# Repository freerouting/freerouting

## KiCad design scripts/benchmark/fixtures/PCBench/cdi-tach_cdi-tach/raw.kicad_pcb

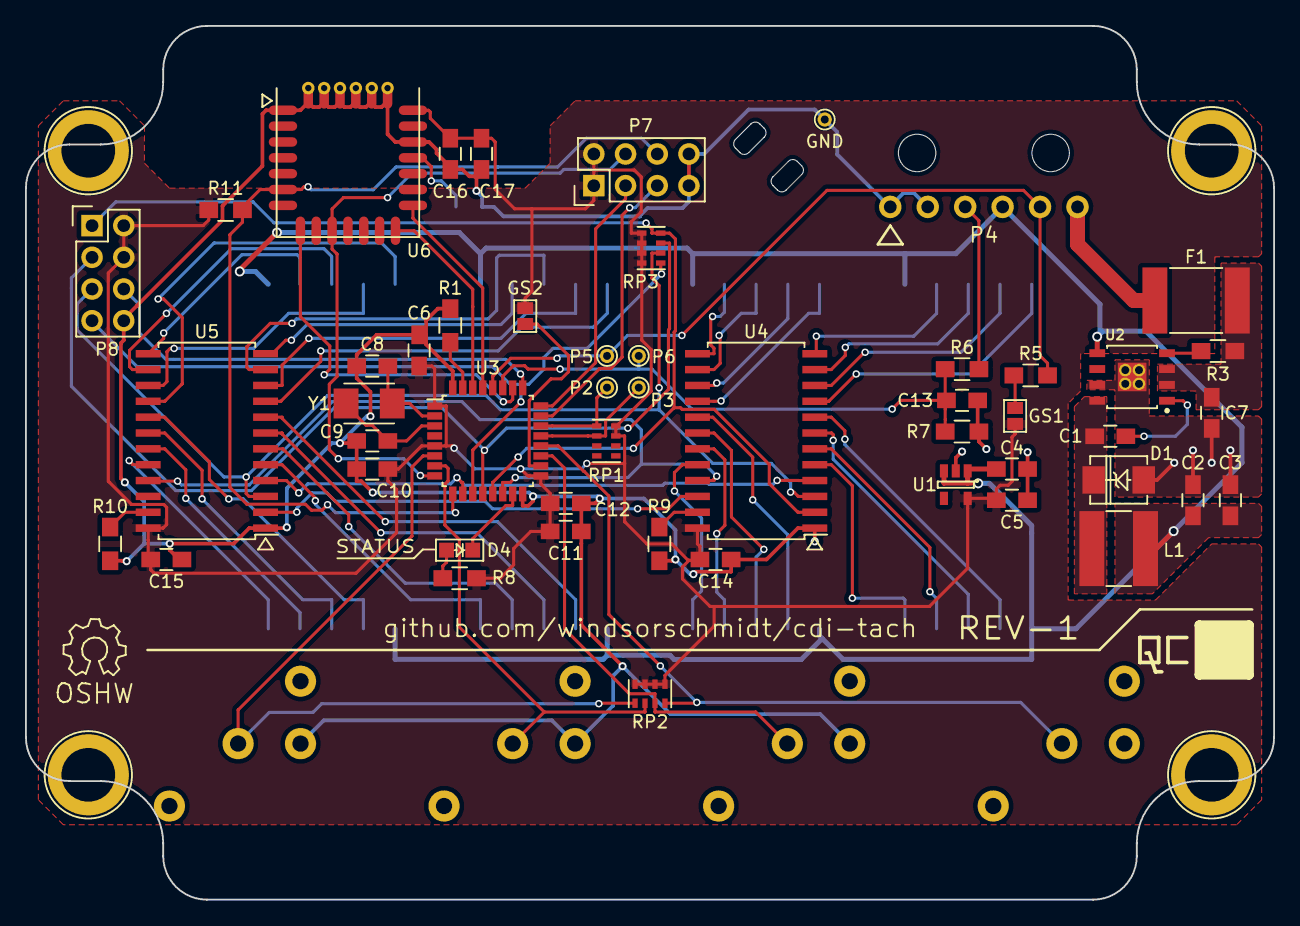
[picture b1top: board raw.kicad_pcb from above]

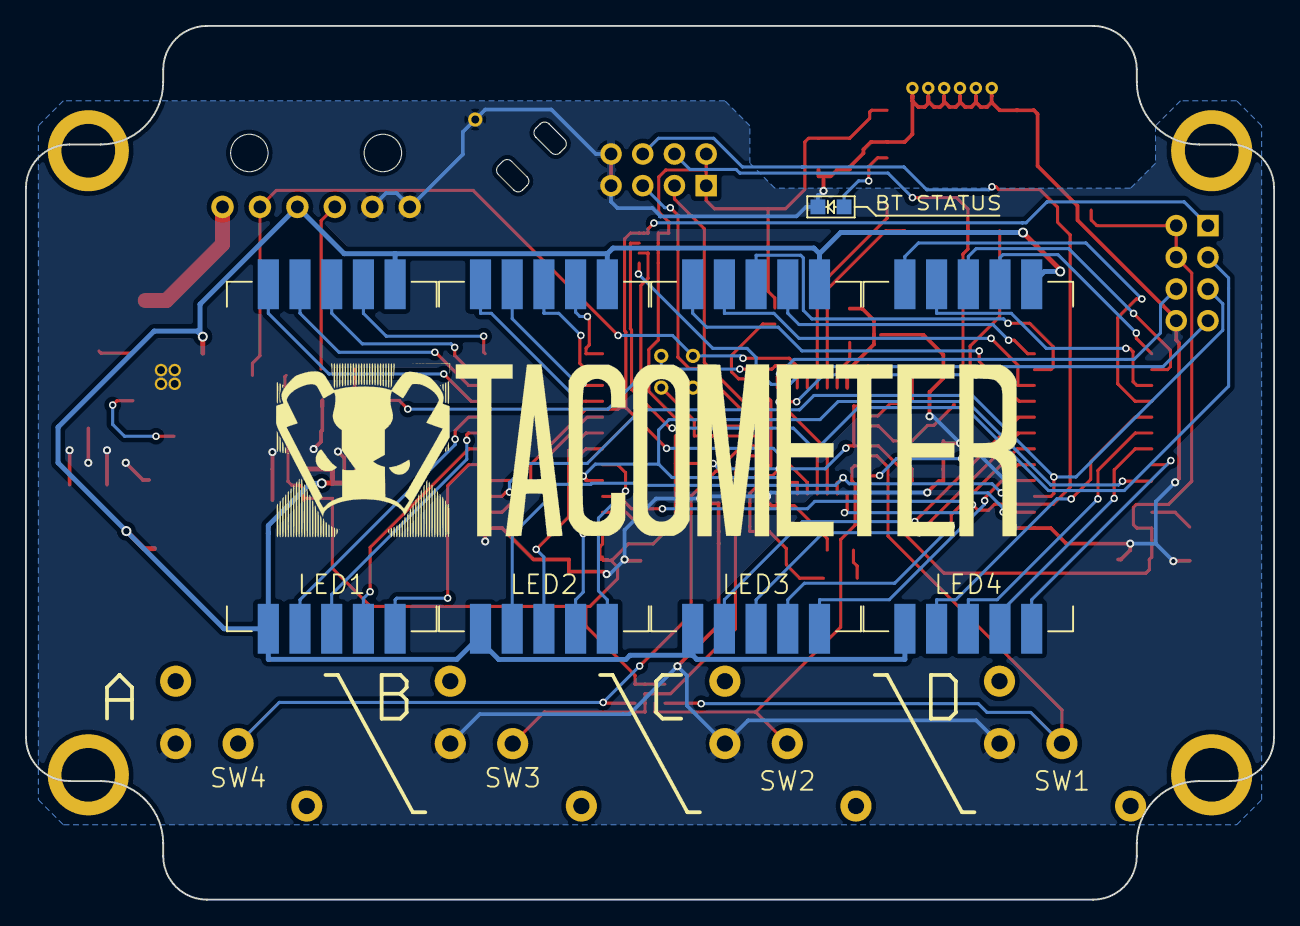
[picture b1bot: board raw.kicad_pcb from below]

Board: 2 copper layers, 100.0 x 70.0 mm, 70 parts (11 on the bottom side), 74 nets.

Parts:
ART1: badger_logo; badger_face_logo
ART2: OSHW_logo; Symbol_OSHW-Logo_SilkScreen
ART3: part_logo; tacometer_logo
ART4: QC_label; label_qc
C1, C6, C10, C12, C17: 100nF; C_0805_HandSoldering
C2, C3: 22uF; C_0805_HandSoldering
C4, C5, C14, C15: 1uF; C_0805_HandSoldering
C7, C16: 10uF; C_0805_HandSoldering
C8, C9: 18pF; C_0805_HandSoldering
C11: 4.7uF; C_0805_HandSoldering
C13: 22nF; C_0805_HandSoldering
D1: SSB44; Diode_SSB44
D4: STATUS; LED_0805
D5: BT STATUS; LED_0805
F1: 3.7A Polyswitch; Fuse_Resettable
GND: GND; PINTST
GS1: SPD_PU; GS2
GS2: MODE; GS2
L1: 6.8uH; Inductor_Bourns_SRN6045_6mm
LED1, LED2, LED3, LED4: ACSA08-51SEKWA
MNT1, MNT6: zip_tie_slot; MOUNT_ZIP_TIE
MNT2, MNT3, MNT4, MNT5: 4mm_screw; Screw_M4
P2: SDA; PINTST
P3: SCL; PINTST
P4: PWR_SPD_TACH; micro-fit_1x6_ra
P5: SPEED; PINTST
P6: TACH; PINTST
P7: DEBUG; Pin_Header_Straight_2x04
P8: LCD; Pin_Header_Straight_2x04
PCB enclosure: PCB_enclosure; pcb_enclosure
R1, R5, R9, R10: 3K; R_0805_HandSoldering
R3, R6: 100K; R_0805_HandSoldering
R7: 12.1K; R_0805_HandSoldering
R8: 39; R_0805_HandSoldering
R11: 10K; R_0805_HandSoldering
RP1, RP2, RP3: 4.7K; R_Cat16-4
SW1: A; pushbutton_marquardt_6450
SW2: B; pushbutton_marquardt_6450
SW3: C; pushbutton_marquardt_6450
SW4: D; pushbutton_marquardt_6450
U1: MIC5504-3.3YM5; SOT-23-5
U2: ADP2302ARDZ-5.0; ADP2302_SOIC8
U3: STM32F030K6T6; LQFP-32_7x7mm_Pitch0.8mm
U4, U5: CAT4016; SOIC-24_7.5x15.4mm_Pitch1.27mm
U6: AMS002-S
Y1: 7A-8.000MAAE-T; crystal_txc_7a_5x3.2mm

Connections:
+3V3: C5.1, C6.2, C10.2, C11.1, C12.1, C14.2, C15.2, C16.1, C17.1, GS1.2, GS2.2, P7.1, P7.2, P8.2, P8.4, R8.2, R11.1, RP1.7, RP1.8, RP2.5, RP2.6, RP2.7, RP2.8, RP3.1, RP3.2, RP3.3, RP3.4, U1.5, U3.1, U3.5, U3.17, U4.24, U5.24, U6.21
+5V: C2.1, C3.1, C4.1, L1.2, LED1.1, LED1.6, LED2.1, LED2.6, LED3.1, LED3.6, LED4.1, LED4.6, P4.3, U1.1, U1.3, U2.5
+12V: F1.1, P4.1
BTN_A: RP2.1, SW1.1, U3.6
BTN_B: RP2.2, SW2.1, U3.7
BTN_C: RP2.3, SW3.1, U3.19
BTN_D: RP2.4, SW4.1, U3.20
BT_CONN: U3.29, U6.15
BT_NRST: U3.26, U6.8
BT_STRM: U3.30, U6.14
GND: C2.2, C3.2, C4.2, C5.2, C6.1, C7.1, C8.1, C9.1, C10.1, C11.2, C12.2, C13.1, C14.1, C15.1, C16.2, C17.2, D1.1, D5.1, GND.1, P4.5, P4.6, P7.7, P7.8, P8.8, R1.2, R7.2, R9.2, R10.2, SW1.2, SW2.2, SW3.2, SW4.2, U1.2, U2.7, U2.9, U3.16, U3.32, U4.1, U5.1, U6.1, U6.19, U6.22, U6.23, U6.24, U6.25, U6.26, U6.27
LCD_RST: P8.6, U3.25
LED1_A: LED1.8, U4.11
LED1_B: LED1.7, U4.12
LED1_C: LED1.4, U4.6
LED1_D: LED1.3, U4.7
LED1_DP: LED1.5, U4.5
LED1_E: LED1.2, U4.8
LED1_F: LED1.9, U4.10
LED1_G: LED1.10, U4.9
LED2_A: LED2.8, U4.14
LED2_B: LED2.7, U4.13
LED2_C: LED2.4, U4.19
LED2_D: LED2.3, U4.18
LED2_DP: LED2.5, U4.20
LED2_E: LED2.2, U4.17
LED2_F: LED2.9, U4.15
LED2_G: LED2.10, U4.16
LED3_A: LED3.8, U5.11
LED3_B: LED3.7, U5.12
LED3_C: LED3.4, U5.6
LED3_D: LED3.3, U5.7
LED3_DP: LED3.5, U5.5
LED3_E: LED3.2, U5.8
LED3_F: LED3.9, U5.10
LED3_G: LED3.10, U5.9
LED4_A: LED4.8, U5.14
LED4_B: LED4.7, U5.13
LED4_C: LED4.4, U5.19
LED4_D: LED4.3, U5.18
LED4_DP: LED4.5, U5.20
LED4_E: LED4.2, U5.17
LED4_F: LED4.9, U5.15
LED4_G: LED4.10, U5.16
LED_BLANK: U3.14, U4.21, U5.21
LED_LATCH: U3.10, U4.4, U5.4
unnamed: C1.1, D1.2, L1.1, U2.8
unnamed: C1.2, U2.1
unnamed: C7.2, F1.2, R3.2, U2.2, U2.3
unnamed: C8.2, U3.2, Y1.2
unnamed: C9.2, U3.3, Y1.1
unnamed: D4.1, U3.15
unnamed: D4.2, R8.1
unnamed: D5.2, U6.18
unnamed: GS1.1, R5.2
unnamed: GS2.1, U3.18
unnamed: P2.1, RP1.1, U3.22
unnamed: P3.1, RP1.2, U3.21
unnamed: P4.4, R6.1
unnamed: R1.1, U3.31
unnamed: R3.1, U2.4
unnamed: R9.1, U4.23
unnamed: R10.1, U5.23
unnamed: U4.22, U5.2
SPEED: P4.2, P5.1, R5.1, U3.28
SPI_CS: P8.7, RP3.5, U3.11
SPI_MISO: P8.3, RP3.7, U3.12
SPI_MOSI: P8.1, RP3.8, U3.13, U4.2
SPI_SCK: P8.5, RP3.6, U4.3, U5.3
SWCLK: P7.3, U3.24
SWDIO: P7.5, U3.23
TACH: C13.2, P6.1, R6.2, R7.1, U3.27
USART_RX: P7.6, R11.2, U3.9, U6.6
USART_TX: P7.4, U3.8, U6.10

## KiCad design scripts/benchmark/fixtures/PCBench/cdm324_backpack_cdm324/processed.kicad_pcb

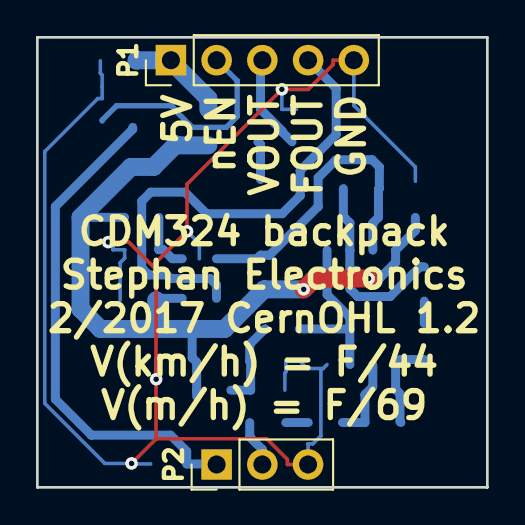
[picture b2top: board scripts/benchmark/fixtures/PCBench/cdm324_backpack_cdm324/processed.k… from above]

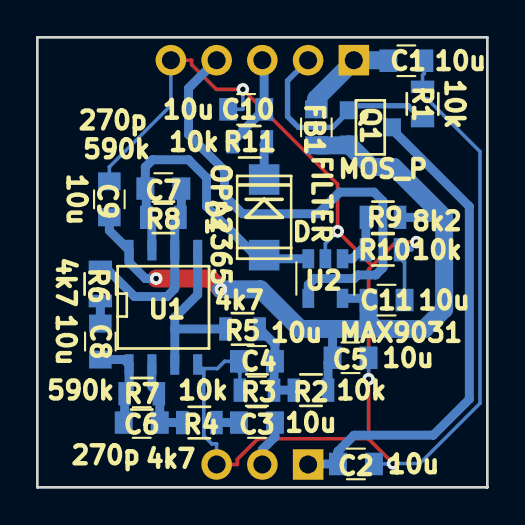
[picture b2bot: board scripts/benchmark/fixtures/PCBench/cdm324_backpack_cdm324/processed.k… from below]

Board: 2 copper layers, 25.0 x 25.0 mm, 29 parts (27 on the bottom side), 18 nets.

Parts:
C1, C2, C3, C4, C5, C8, C9, C10, C11: 10u; C_0805
C6, C7: 270p; C_0805
D1: D; DIODE_SMA
FB1: FILTER; C_0805
P1: CONN_01X05; Pin_Header_Straight_1x05_Pitch2.54mm
P2: CONN_01X03; Pin_Header_Straight_1x03_Pitch2.54mm
Q1: MOS_P; SOT23-3
R1, R2, R3, R10, R11: 10k; R_0805
R4, R5, R6: 4k7; R_0805
R7, R8: 590k; R_0805
R9: 8k2; R_0805
U1: OPA2365; SOIC-8-N
U2: MAX9031; SOT-23-5

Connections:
+5V: C1.1, FB1.1, P1.1
/FOUT: P1.4, U2.4
/VOUT: C10.1, P1.3, R11.2
/nEN: P1.2, Q1.1, R1.1
GND: C1.2, C2.2, C4.2, C5.2, C9.2, C10.2, C11.2, P1.5, P2.3, R1.2, R3.2, R10.2, U1.4, U2.2
unnamed: C2.1, P2.1, Q1.3
unnamed: C3.1, P2.2
unnamed: C3.2, R4.1
unnamed: C4.1, R2.2, R3.1, R5.1
unnamed: C6.1, R4.2, R7.1, U1.2
unnamed: C6.2, C8.2, R7.2, U1.1
unnamed: C7.1, R6.1, R8.2, U1.6
unnamed: C7.2, D1.2, R8.1, U1.7, U2.3
unnamed: C8.1, R6.2
unnamed: C5.1, C9.1, C11.1, FB1.2, Q1.2, R2.1, R9.1, U1.8, U2.5
unnamed: D1.1, R11.1
unnamed: R5.2, U1.3, U1.5
unnamed: R9.2, R10.1, U2.1

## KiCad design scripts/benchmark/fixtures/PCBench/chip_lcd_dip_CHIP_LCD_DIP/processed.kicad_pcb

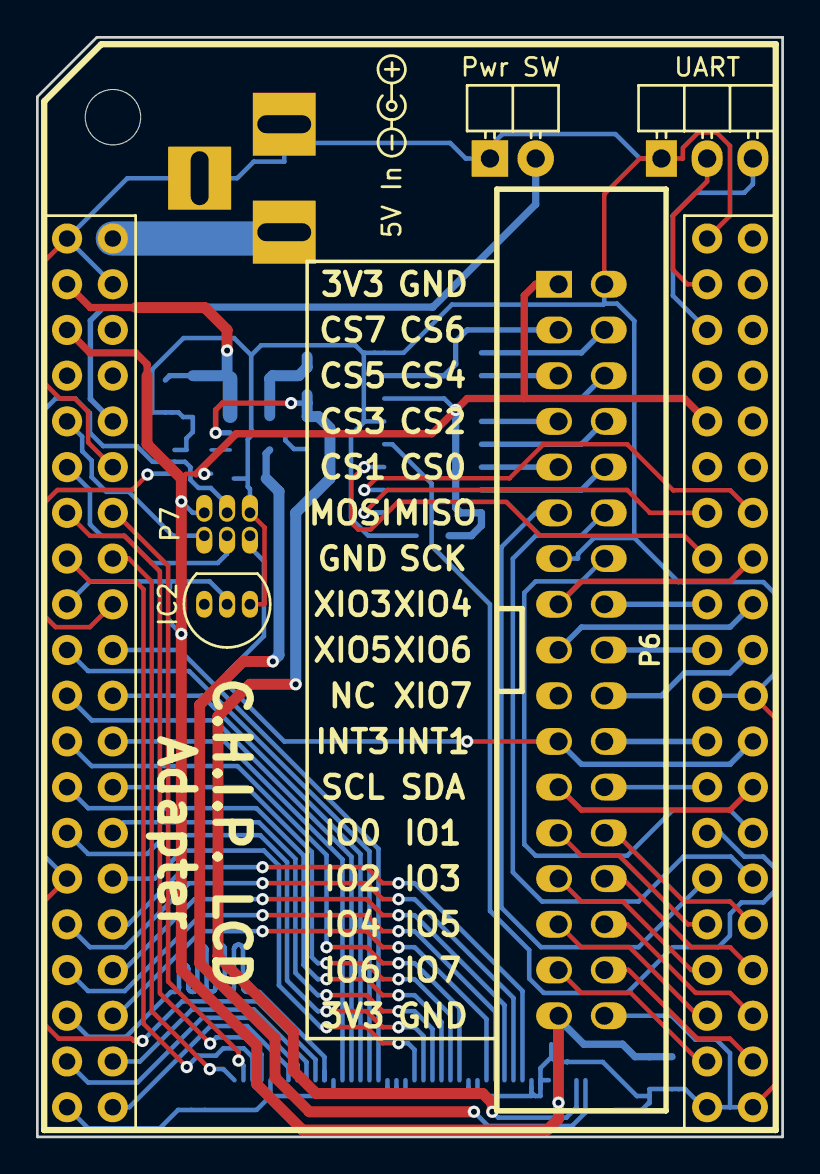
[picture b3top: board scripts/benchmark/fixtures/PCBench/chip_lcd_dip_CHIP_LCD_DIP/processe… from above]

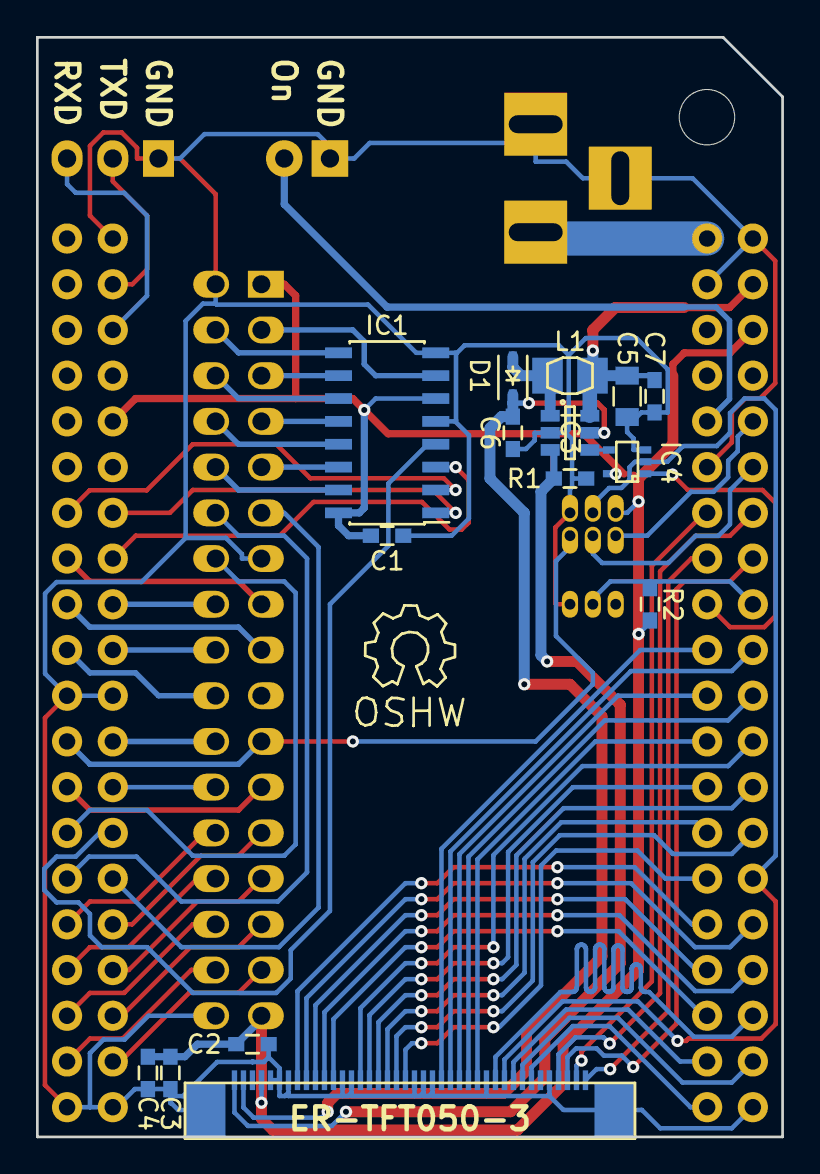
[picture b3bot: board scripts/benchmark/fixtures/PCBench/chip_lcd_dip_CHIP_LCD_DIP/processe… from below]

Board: 2 copper layers, 41.4 x 61.1 mm, 22 parts (15 on the bottom side), 72 nets.

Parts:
C1, C2, C7: 0.1µF; C_0603
C3, C6: 1µF; C_0603
C4: 10µF; C_0603
C5: 10µF; C_0805
D1: DB2J40700; SOD-323
IC1: 74LVC138; SOIC-16_3.9x9.9mm_Pitch1.27mm
IC2: DS2431; TO-92_Inline_Narrow_Oval
IC3: AP3032; SOT-23-6
IC4: 74AHC1G08; SC-70-5
L1: 6.8µH; TDK_VLS-E-CA
P1: C.H.I.P.; CHIP_DIP
P2: Power; BARREL_JACK
P3: Pwr SW; Pin_Header_Angled_1x02
P4: UART; Pin_Header_Angled_1x03
P5: LCD; TE_40_PIN_LCD_Connector
P6: GPIO; vasch_strip_17x2
P7: TS; 02x03_Header_0.05
R1: 5.6Ω; C_0603
R2: 4.7K; C_0603

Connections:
+3V3: C1.1, C2.1, C3.1, C4.1, IC1.6, IC1.16, IC4.5, P1.5, P1.49, P5.4, P6.1, P6.33, P7.2, R2.1
+5V: C5.1, C7.1, IC3.6, L1.1, P1.3
/1W: IC2.2, P1.17, R2.2
/B3: P1.20, P5.24
/B4: P1.19, P5.25
/B5: P1.22, P5.26
/B6: P1.21, P5.27
/B7: P1.24, P5.28
/CS: IC1.4, P1.67
/CS0: IC1.15, P6.10
/CS1: IC1.14, P6.9
/CS2: IC1.13, P6.8
/CS3: IC1.12, P6.7
/CS4: IC1.11, P6.6
/CS5: IC1.10, P6.5
/CS6: IC1.9, P6.4
/CS7: IC1.7, P6.3
/CSADDR0: IC1.1, P1.53
/CSADDR1: IC1.2, P1.54
/CSADDR2: IC1.3, P1.55
/DEN: P1.40, P5.34
/G2: P1.23, P5.15
/G3: P1.26, P5.16
/G4: P1.25, P5.17
/G5: P1.28, P5.18
/G6: P1.27, P5.19
/G7: P1.30, P5.20
/HSYNC: P1.38, P5.32
/INT1: P1.63, P6.22
/INT3: P1.64, P6.21, P7.5
/IO0: P1.71, P6.25
/IO1: P1.72, P6.26
/IO2: P1.73, P6.27
/IO3: P1.74, P6.28
/IO4: P1.75, P6.29
/IO5: P1.76, P6.30
/IO6: P1.77, P6.31
/IO7: P1.78, P6.32
/LCD_ON: IC4.2, P1.29, P5.31, P7.4
/LEDA: C6.1, D1.1, IC3.5, P5.2
/LEDK: IC3.3, P5.1, R1.1
/MISO: P1.70, P6.12
/MOSI: P1.69, P6.11
/On: P1.10, P3.2
/PWM: IC4.1, P1.18
/PXCLK: P1.35, P5.30
/R3: P1.32, P5.8
/R4: P1.31, P5.9
/R5: P1.34, P5.10
/R6: P1.33, P5.11
/R7: P1.36, P5.12
/RXD1: P1.45, P4.3
/SCK: P1.68, P6.14
/SCL1: P1.11, P7.3
/SCL2: P1.66, P6.23
/SDA1: P1.9, P7.1
/SDA2: P1.65, P6.24
/TXD1: P1.43, P4.2
/VSYNC: P1.37, P5.33
/Vin+: P1.2, P2.1
/X1: P1.13, P5.37
/X2: P1.14, P5.39
/XIO3: P1.56, P6.15
/XIO4: P1.57, P6.16
/XIO5: P1.58, P6.17
/XIO6: P1.59, P6.18
/XIO7: P1.60, P6.20
/Y1: P1.15, P5.38
/Y2: P1.16, P5.40
GND: C1.2, C2.2, C3.2, C4.2, C5.2, C6.2, C7.2, IC1.5, IC1.8, IC2.1, IC3.2, IC4.3, P1.1, P1.4, P1.12, P1.39, P1.41, P1.61, P1.62, P1.79, P1.80, P2.2, P2.3, P3.1, P4.1, P5.3, P5.5, P5.6, P5.7, P5.13, P5.14, P5.21, P5.22, P5.23, P5.29, P5.36, P6.2, P6.13, P6.34, P7.6, R1.2
unnamed: D1.2, IC3.1, L1.2
unnamed: IC3.4, IC4.4
